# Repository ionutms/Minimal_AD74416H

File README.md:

# Minimal_AD74416H

## Overview

This repository contains a minimal KiCad design project for the Analog Devices AD74416H, a quad-channel, software-configurable input and output device with HART modem capabilities. The project includes schematic designs and PCB layout files for implementing this versatile analog I/O device.

## Disclaimer

> [!NOTE]
> This project is provided "as is" and without any warranty, express or implied. For more details, please see the [LICENSE](LICENSE) file.

## About the AD74416H

The AD74416H from Analog Devices is a quad-channel, software-configurable input/output solution for building and process control applications. It integrates a 24-bit, sigma-delta (Σ-Δ) analog-to-digital converter (ADC) and four 16-bit digital-to-analog converters (DACs).

Key features include:

- **Software-Configurable Channels:** Each of the four channels can be independently configured as:
  - Analog Input (Voltage or Current)
  - Analog Output (Voltage or Current)
  - Digital Input
  - Digital Output
  - 2- or 3-wire Resistance Temperature Detector (RTD) and Thermocouple measurements
- **HART Compatibility:** Each channel has an integrated HART (Highway Addressable Remote Transducer) modem.
- **Integrated Converters:** The device includes a 16-bit digital-to-analog converter (DAC) per channel and a single 24-bit sigma-delta (Σ-Δ) analog-to-digital converter (ADC).
- **Communication:** All input, output, and HART communications for the four channels are handled through a single SPI-compatible interface. It is possible to address up to four AD74416H devices on a single SPI bus.
- **Power Efficiency:** It features adaptive power switching, which can lower power dissipation by up to 40%.
- **Robustness and Diagnostics:** Features on-chip diagnostics like open-circuit and short-circuit detection and an internal temperature sensor.
- **Operating Temperature Range:** -40°C to +105°C.
- **Package:** Available in a 64-lead LFCSP package.

## Project Structure

```
minimal_ad74416h/
├── minimal_ad74416h.kicad_pro                     # Project configuration file
├── minimal_ad74416h.kicad_sch                     # Main schematic file
├── AD74416H.kicad_sch                             # AD74416H symbol definition
├── Front End Channel 1.kicad_sch                  # Channel-specific schematic
├── Power Supply and Digital Interface.kicad_sch   # Power and interface schematic
├── minimal_ad74416h.kicad_pcb                     # PCB layout file
├── fp-lib-table                                   # Footprint library table
├── sym-lib-table                                  # Symbol library table
├── docs/                                          # Documentation files
│   ├── bom/                                       # Bill of Materials
│   │   └── minimal_ad74416h_ibom.html             # Interactive BOM file
│   ├── pictures/                                  # Images and photos
│   │   ├── 1_minimal_ad74416h_side.png            # Side view of PCB
│   │   ├── 2_minimal_ad74416h_top.png             # Top view of PCB
│   │   └── 3_minimal_ad74416h_bottom.png          # Bottom view of PCB
│   └── schematics/                                # Schematic PDF exports
│       └── minimal_ad74416h_schematics.pdf        # Complete schematics PDF
└── KiCAD_Symbols_Generator/                       # Submodule for symbol generation from CSV data
```

## Project Features

This design provides a minimal implementation of the AD74416H with:

- Proper power supply connections
- Reference voltage generation
- Basic channel configuration
- HART communication interface
- Standard footprint for the 64-pin LFCSP package

## Getting Started

### Prerequisites

- [KiCad EDA](https://www.kicad.org/) version 9.0 or later installed on your system
- Git (for cloning the repository and submodule management)

### Opening the Project

1. **Clone the repository** (including submodules):
   ```bash
   git clone --recursive https://github.com/ionutms/Minimal_AD74416H.git
   ```
   
   If you've already cloned the repository without submodules, initialize them with:
   ```bash
   git submodule init
   git submodule update
   ```

2. **Open the project in KiCad**:
   - Launch KiCad
   - Click "Open Existing Project"
   - Navigate to the cloned repository folder
   - Select the `minimal_ad74416h.kicad_pro` file

3. **Explore the design**:
   - Open the schematic editor to view the circuit design
   - Open the PCB editor to view the board layout
   - Review the symbol and footprint libraries used in the design

### Project Files

- **Main schematic**: `minimal_ad74416h.kicad_sch` - Contains the primary circuit design with the AD74416H and support components
- **Channel schematic**: `Front End Channel 1.kicad_sch` - Detailed implementation of one channel with protection and filtering
- **Power schematic**: `Power Supply and Digital Interface.kicad_sch` - Power supply and digital interface circuits
- **PCB layout**: `minimal_ad74416h.kicad_pcb` - Physical board design file with proper component placement
- **Project configuration**: `minimal_ad74416h.kicad_pro` - KiCad project settings

## Dependencies

This project has the following dependencies:

### 1. KiCAD Symbols Generator

This repository uses [KiCAD_Symbols_Generator](https://github.com/ionutms/KiCAD_Symbols_Generator) as a submodule for custom symbol generation.

To initialize the submodule after cloning this repository:

```bash
git submodule update --init --recursive
```

### 2. 3D Models

This project requires the [3D_Models_Vault](https://github.com/ionutms/3D_Models_Vault) repository for 3D models.

#### Setup for KiCAD 9:

1. Clone the 3D models repository:
   ```bash
   git clone https://github.com/ionutms/3D_Models_Vault.git
   ```

2. In KiCAD 9, add an environment variable:
   - Variable name: `KICAD9_3D_MODELS_VAULT`
   - Variable value: Full path to where you cloned the 3D_Models_Vault repository

## Usage

After setting up the dependencies, open the project in KiCad 9 to access all features including the 3D models.

## Symbol Generator Submodule

This project includes the KiCAD_Symbols_Generator as a submodule, which provides tools for generating KiCad symbols from CSV data files. For more information on using this tool, see the [KiCAD_Symbols_Generator documentation](minimal_ad74416h/KiCAD_Symbols_Generator/README.md).

## Documentation

The `docs` folder contains:
- Schematic PDF exports
- Images and photos of the design

## Visuals

The following images showcase the PCB design from different perspectives:

*Top View of the PCB*

*Side View of the PCB*

*Bottom View of the PCB*

## License

This project is licensed under the MIT License - see the [LICENSE](LICENSE) file for details.

## References

- [AD74416H Datasheet](https://www.analog.com/media/en/technical-documentation/data-sheets/ad74416h.pdf)
- [KiCad EDA](https://www.kicad.org/)

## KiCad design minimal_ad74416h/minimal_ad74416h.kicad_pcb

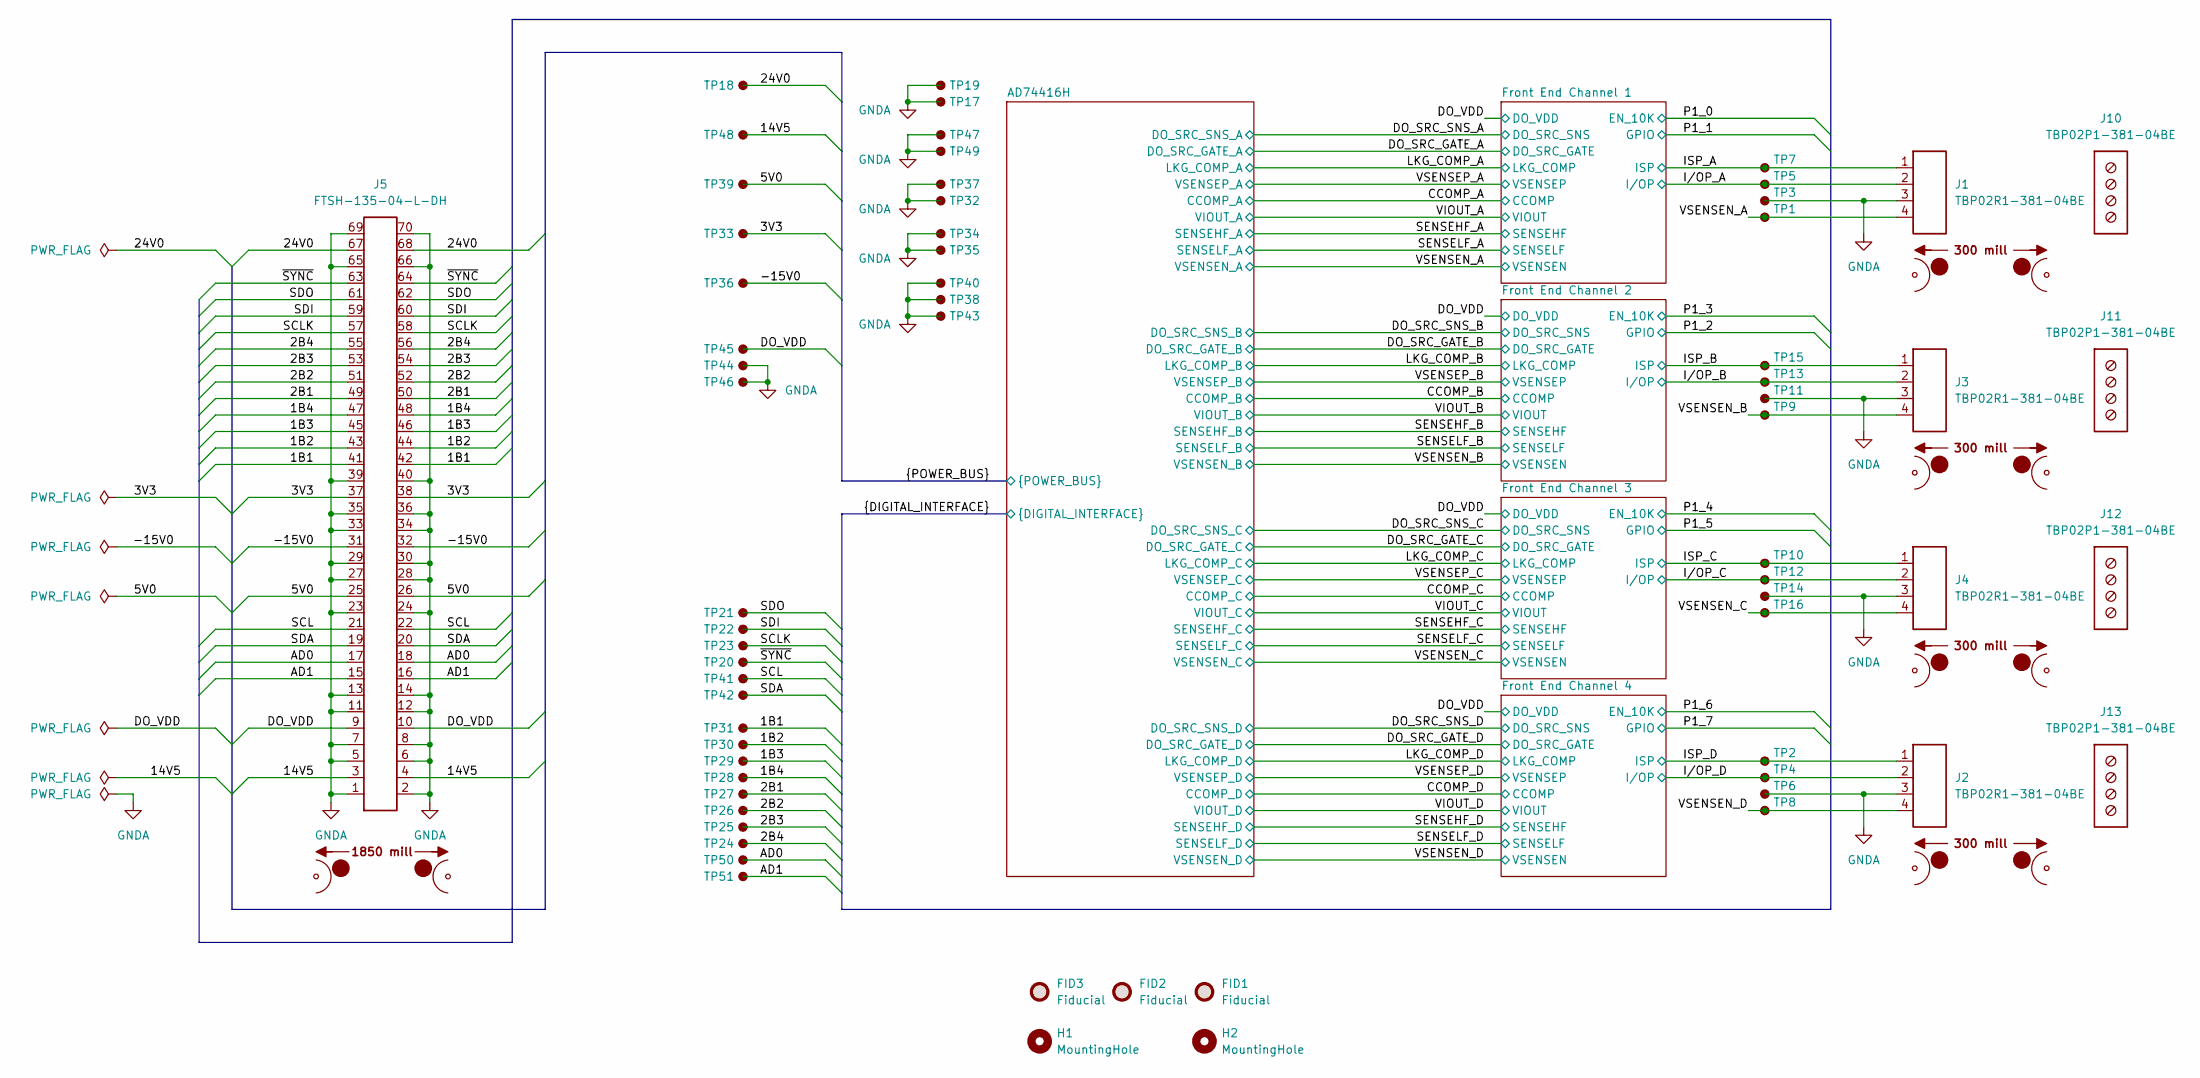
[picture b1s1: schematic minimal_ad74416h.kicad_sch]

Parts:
FID1, FID2, FID3: Fiducial; Fiducial_0.5mm_Mask1mm
H1, H2: MountingHole; MountingHole_3.2mm_M3
J1, J2, J3, J4: TBP02R1-381-04BE; Current Rating (A) 8.0; Voltage Rating (V) 300; MPN TBP02R1-381-04BE
J5: FTSH-135-04-L-DH; Current Rating (A) 5.2; Voltage Rating (V) 300; MPN FTSH-135-04-L-DH
J10, J11, J12, J13: TBP02P1-381-04BE; Current Rating (A) 8.0; Voltage Rating (V) 300; MPN TBP02P1-381-04BE
MB1, MB2, MB3, MB4: mouse-bite-50mil-300mil
MB5: mouse-bite-50mil-1850mil
TP1, TP2, TP3, TP4, TP5, TP6, TP7, TP8, TP9, TP10, TP11, TP12, TP13, TP14, TP15, TP16, TP17, TP18, TP19, TP20, TP21, TP22, TP23, TP24, TP25, TP26, TP27, TP28, TP29, TP30, TP31, TP32, TP33, TP34, TP35, TP36, TP37, TP38, TP39, TP40, TP41, TP42, TP43, TP44, TP45, TP46, TP47, TP48, TP49, TP50, TP51: TestPoint; TestPoint_THTPad_Castelated

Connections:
/1B1: J5.41, J5.42, TP31.1; also elsewhere on the board
/1B2: J5.43, J5.44, TP30.1; also elsewhere on the board
/1B3: J5.45, J5.46, TP29.1; also elsewhere on the board
/1B4: J5.47, J5.48, TP28.1; also elsewhere on the board
/2B1: J5.49, J5.50, TP27.1; also elsewhere on the board
/2B2: J5.51, J5.52, TP26.1; also elsewhere on the board
/2B3: J5.53, J5.54, TP25.1; also elsewhere on the board
/2B4: J5.55, J5.56, TP24.1; also elsewhere on the board
/3V3: J5.37, J5.38, TP33.1; also elsewhere on the board
/5V0: J5.25, J5.26, TP39.1; also elsewhere on the board
/14V5: J5.3, J5.4, TP48.1; also elsewhere on the board
/24V0: J5.67, J5.68, TP18.1; also elsewhere on the board
/-15V0: J5.31, J5.32, TP36.1; also elsewhere on the board
/AD0: J5.17, J5.18, TP50.1; also elsewhere on the board
/AD1: J5.15, J5.16, TP51.1; also elsewhere on the board
/DO_VDD: J5.9, J5.10, TP45.1; also elsewhere on the board
/ISP_A: J1.1, TP7.1; also elsewhere on the board
/ISP_B: J3.1, TP15.1; also elsewhere on the board
/ISP_C: J4.1, TP10.1; also elsewhere on the board
/ISP_D: J2.1, TP2.1; also elsewhere on the board
/I/OP_A: J1.2, TP5.1; also elsewhere on the board
/I/OP_B: J3.2, TP13.1; also elsewhere on the board
/I/OP_C: J4.2, TP12.1; also elsewhere on the board
/I/OP_D: J2.2, TP4.1; also elsewhere on the board
/SCL: J5.21, J5.22, TP41.1; also elsewhere on the board
/SCLK: J5.57, J5.58, TP23.1; also elsewhere on the board
/SDA: J5.19, J5.20, TP42.1; also elsewhere on the board
/SDI: J5.59, J5.60, TP22.1; also elsewhere on the board
/SDO: J5.61, J5.62, TP21.1; also elsewhere on the board
/VSENSEN_A: J1.4, TP1.1; also elsewhere on the board
/VSENSEN_B: J3.4, TP9.1; also elsewhere on the board
/VSENSEN_C: J4.4, TP16.1; also elsewhere on the board
/VSENSEN_D: J2.4, TP8.1; also elsewhere on the board
/~SYNC: J5.63, J5.64, TP20.1; also elsewhere on the board
GNDA: J1.3, J2.3, J3.3, J4.3, J5.1, J5.2, J5.5, J5.6, J5.7, J5.8, J5.11, J5.12, J5.13, J5.14, J5.23, J5.24, J5.27, J5.28, J5.29, J5.30, J5.33, J5.34, J5.35, J5.36, J5.39, J5.40, J5.65, J5.66, J5.69, J5.70, TP3.1, TP6.1, TP11.1, TP14.1, TP17.1, TP19.1, TP32.1, TP34.1, TP35.1, TP37.1, TP38.1, TP40.1, TP43.1, TP44.1, TP46.1, TP47.1, TP49.1; also elsewhere on the board

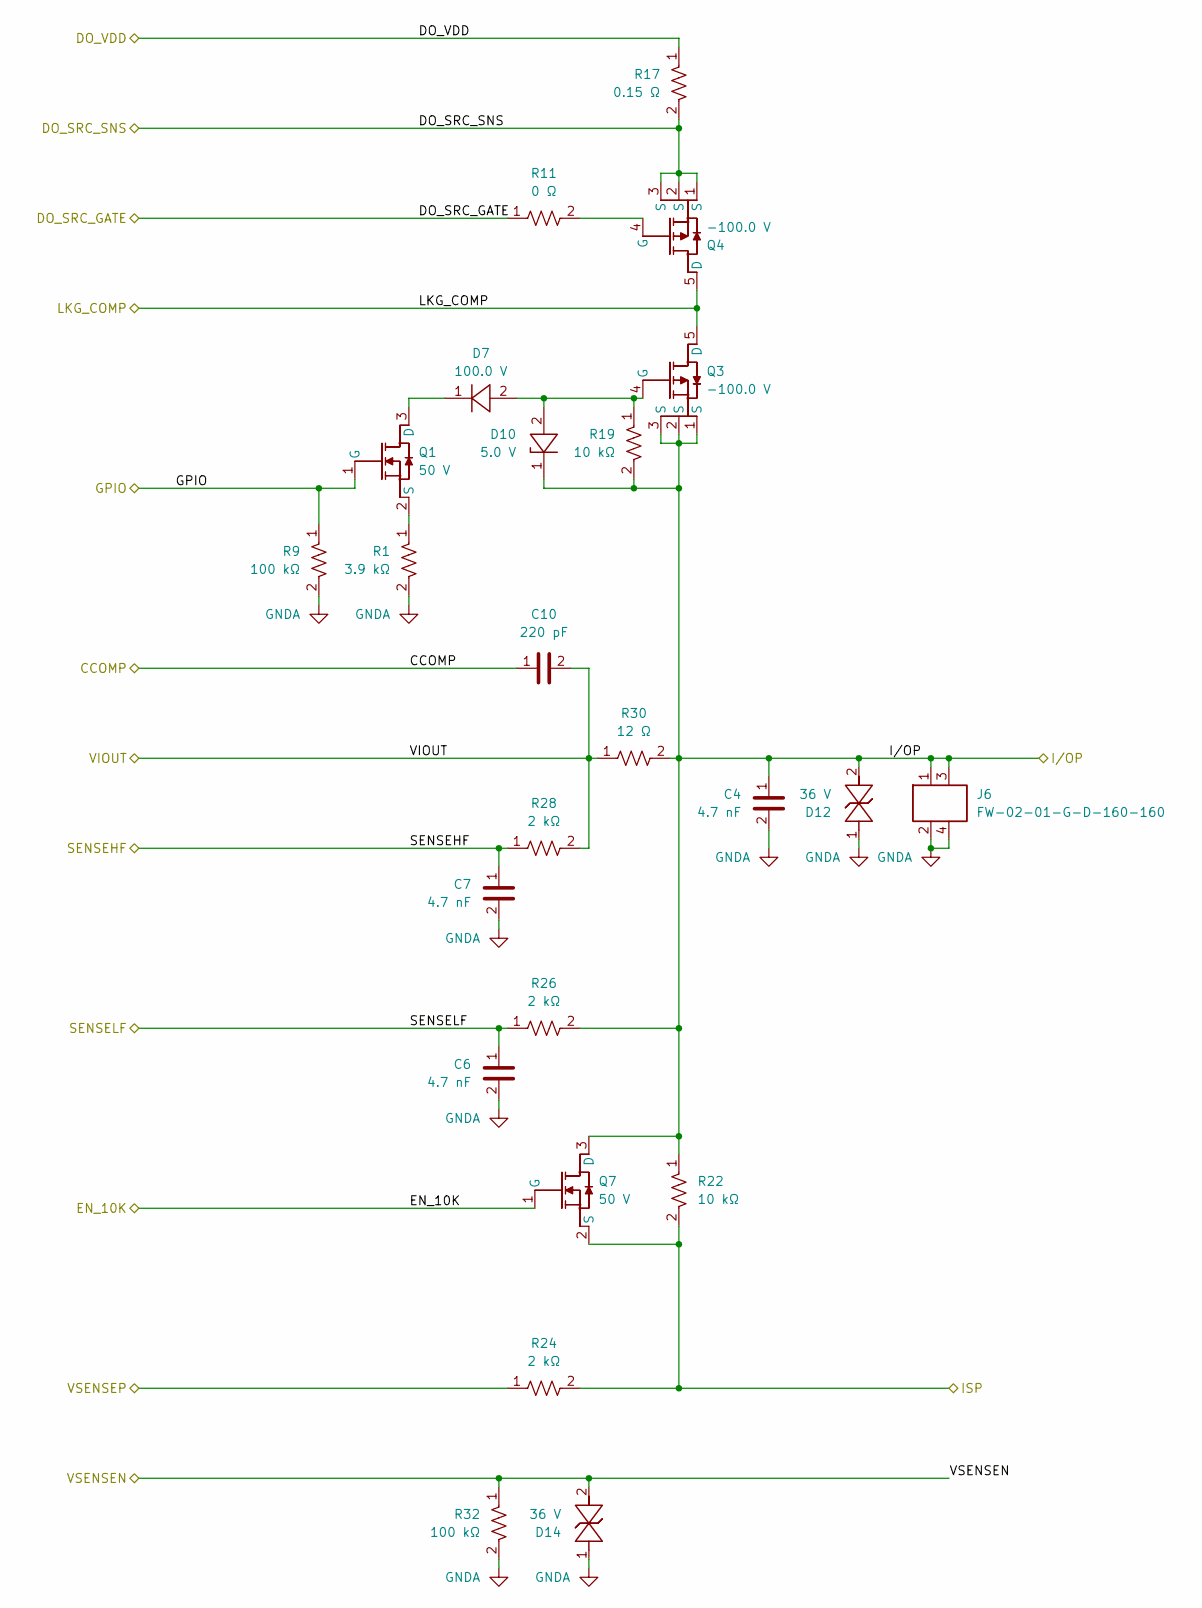
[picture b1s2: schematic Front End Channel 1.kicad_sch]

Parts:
C4, C6, C7: 4.7 nF; C_0603_1608Metric; Tolerance 10%; Voltage Rating 100V; MPN VJ0603Y472KXBAC
C10: 220 pF; C_0603_1608Metric; Tolerance 5%; Voltage Rating 50V; MPN CC0603JRNPO9BN221
D7: 100.0 V; DO-219AD; MPN MSE1PB-M3/89A
D10: 5.0 V; SOD323; MPN ESD9M5.0ST5G
D12, D14: 36 V; DO-214AA; MPN SMBJ36CA
J6: FW-02-01-G-D-160-160; Current Rating (A) 5.2; Voltage Rating (V) 300; MPN FW-02-01-G-D-160-160
Q1, Q7: 50 V; SOT23-3; MPN BSS138-7-F
Q3, Q4: -100.0 V; PowerPAK 1212-8; MPN SI7113ADN-T1-GE3
R1: 3.9 kΩ; R_0402_1005Metric; Tolerance 1%; Voltage Rating 50V; MPN ERJ-2RKF3901X
R9, R32: 100 kΩ; R_0402_1005Metric; Tolerance 5%; Voltage Rating 50V; MPN RMCF0402JT100K
R11: 0 Ω; R_0402_1005Metric; Tolerance 5%; Voltage Rating 50V; MPN ERJ-2GE0R00X
R17: 0.15 Ω; R_1206_3216Metric; Tolerance 1%; Voltage Rating 200; MPN CRM1206-FX-R150ELF
R19, R22: 10 kΩ; R_0402_1005Metric; Voltage Rating 50V; Tolerance 1%; MPN ERJ-2RKF1002X
R24, R26: 2 kΩ; R_0402_1005Metric; Tolerance 1%; Voltage Rating 50V; MPN ERJ-2RKF2001X
R28: 2 kΩ; R_0603_1608Metric; Tolerance 0.01%; Voltage Rating 75V; MPN RNCF0603TKY2K00
R30: 12 Ω; R_0805_2012Metric; Tolerance 0.1%; Voltage Rating 150V; MPN RT0805BRB0712RL

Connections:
/CCOMP_A: C10.1; also elsewhere on the board
/DO_SRC_GATE_A: R11.1; also elsewhere on the board
/DO_SRC_SNS_A: Q4.1 (S), Q4.2 (S), Q4.3 (S), R17.2; also elsewhere on the board
/DO_VDD: R17.1; also elsewhere on the board
/ISP_A: Q7.2 (S), R22.2, R24.2; also elsewhere on the board
/I/OP_A: C4.1, D10.1, D12.2, J6.1, J6.3, Q3.1 (S), Q3.2 (S), Q3.3 (S), Q7.3 (D), R19.2, R22.1, R26.2, R30.2; also elsewhere on the board
/LKG_COMP_A: Q3.5 (D), Q4.5 (D); also elsewhere on the board
/P1_0: Q7.1 (G); also elsewhere on the board
/P1_1: Q1.1 (G), R9.1; also elsewhere on the board
/SENSEHF_A: C7.1, R28.1; also elsewhere on the board
/SENSELF_A: C6.1, R26.1; also elsewhere on the board
/VIOUT_A: C10.2, R28.2, R30.1; also elsewhere on the board
/VSENSEN_A: D14.2, R32.1; also elsewhere on the board
/VSENSEP_A: R24.1; also elsewhere on the board
GNDA: C4.2, C6.2, C7.2, D12.1, D14.1, J6.2, J6.4, R1.2, R9.2, R32.2; also elsewhere on the board
unnamed: D7.1, Q1.3 (D)
unnamed: Q1.2 (S), R1.1
unnamed: D7.2, D10.2, Q3.4 (G), R19.1
unnamed: Q4.4 (G), R11.2

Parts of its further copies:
C5, C8, C9, C19, C20, C21, C22, C23, C24: 4.7 nF; C_0603_1608Metric; Tolerance 10%; Voltage Rating 100V; MPN VJ0603Y472KXBAC
C11, C16, C17: 220 pF; C_0603_1608Metric; Tolerance 5%; Voltage Rating 50V; MPN CC0603JRNPO9BN221
D8, D22, D23: 100.0 V; DO-219AD; MPN MSE1PB-M3/89A
D11, D20, D21: 5.0 V; SOD323; MPN ESD9M5.0ST5G
D13, D15, D16, D17, D18, D19: 36 V; DO-214AA; MPN SMBJ36CA
J7, J8, J9: FW-02-01-G-D-160-160; Current Rating (A) 5.2; Voltage Rating (V) 300; MPN FW-02-01-G-D-160-160
Q2, Q8, Q9, Q10, Q15, Q16: 50 V; SOT23-3; MPN BSS138-7-F
Q5, Q6, Q11, Q12, Q13, Q14: -100.0 V; PowerPAK 1212-8; MPN SI7113ADN-T1-GE3
R2, R33, R34, R35, R53, R55: 100 kΩ; R_0402_1005Metric; Tolerance 5%; Voltage Rating 50V; MPN RMCF0402JT100K
R10, R52, R56: 3.9 kΩ; R_0402_1005Metric; Tolerance 1%; Voltage Rating 50V; MPN ERJ-2RKF3901X
R12, R23, R44, R45, R47, R50: 10 kΩ; R_0402_1005Metric; Voltage Rating 50V; Tolerance 1%; MPN ERJ-2RKF1002X
R16, R48, R49: 0.15 Ω; R_1206_3216Metric; Tolerance 1%; Voltage Rating 200; MPN CRM1206-FX-R150ELF
R20, R46, R51: 0 Ω; R_0402_1005Metric; Tolerance 5%; Voltage Rating 50V; MPN ERJ-2GE0R00X
R25, R27, R40, R41, R42, R43: 2 kΩ; R_0402_1005Metric; Tolerance 1%; Voltage Rating 50V; MPN ERJ-2RKF2001X
R29, R38, R39: 2 kΩ; R_0603_1608Metric; Tolerance 0.01%; Voltage Rating 75V; MPN RNCF0603TKY2K00
R31, R36, R37: 12 Ω; R_0805_2012Metric; Tolerance 0.1%; Voltage Rating 150V; MPN RT0805BRB0712RL

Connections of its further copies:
/CCOMP_B: C16.1; also elsewhere on the board
/CCOMP_C: C17.1; also elsewhere on the board
/CCOMP_D: C11.1; also elsewhere on the board
/DO_SRC_GATE_B: R46.1; also elsewhere on the board
/DO_SRC_GATE_C: R51.1; also elsewhere on the board
/DO_SRC_GATE_D: R20.1; also elsewhere on the board
/DO_SRC_SNS_B: Q12.1 (S), Q12.2 (S), Q12.3 (S), R49.2; also elsewhere on the board
/DO_SRC_SNS_C: Q13.1 (S), Q13.2 (S), Q13.3 (S), R48.2; also elsewhere on the board
/DO_SRC_SNS_D: Q5.1 (S), Q5.2 (S), Q5.3 (S), R16.2; also elsewhere on the board
/DO_VDD: R16.1, R48.1, R49.1; also elsewhere on the board
/ISP_B: Q9.2 (S), R42.2, R44.2; also elsewhere on the board
/ISP_C: Q10.2 (S), R43.2, R45.2; also elsewhere on the board
/ISP_D: Q8.2 (S), R23.2, R25.2; also elsewhere on the board
/I/OP_B: C23.1, D18.2, D20.1, J7.1, J7.3, Q9.3 (D), Q11.1 (S), Q11.2 (S), Q11.3 (S), R36.2, R40.2, R44.1, R50.2; also elsewhere on the board
/I/OP_C: C24.1, D19.2, D21.1, J8.1, J8.3, Q10.3 (D), Q14.1 (S), Q14.2 (S), Q14.3 (S), R37.2, R41.2, R45.1, R47.2; also elsewhere on the board
/I/OP_D: C5.1, D11.1, D13.2, J9.1, J9.3, Q6.1 (S), Q6.2 (S), Q6.3 (S), Q8.3 (D), R12.2, R23.1, R27.2, R31.2; also elsewhere on the board
/LKG_COMP_B: Q11.5 (D), Q12.5 (D); also elsewhere on the board
/LKG_COMP_C: Q13.5 (D), Q14.5 (D); also elsewhere on the board
/LKG_COMP_D: Q5.5 (D), Q6.5 (D); also elsewhere on the board
/P1_2: Q15.1 (G), R55.1; also elsewhere on the board
/P1_3: Q9.1 (G); also elsewhere on the board
/P1_4: Q10.1 (G); also elsewhere on the board
/P1_5: Q16.1 (G), R53.1; also elsewhere on the board
/P1_6: Q8.1 (G); also elsewhere on the board
/P1_7: Q2.1 (G), R2.1; also elsewhere on the board
/SENSEHF_B: C20.1, R38.1; also elsewhere on the board
/SENSEHF_C: C21.1, R39.1; also elsewhere on the board
/SENSEHF_D: C8.1, R29.1; also elsewhere on the board
/SENSELF_B: C19.1, R40.1; also elsewhere on the board
/SENSELF_C: C22.1, R41.1; also elsewhere on the board
/SENSELF_D: C9.1, R27.1; also elsewhere on the board
/VIOUT_B: C16.2, R36.1, R38.2; also elsewhere on the board
/VIOUT_C: C17.2, R37.1, R39.2; also elsewhere on the board
/VIOUT_D: C11.2, R29.2, R31.1; also elsewhere on the board
/VSENSEN_B: D16.2, R34.1; also elsewhere on the board
/VSENSEN_C: D17.2, R35.1; also elsewhere on the board
/VSENSEN_D: D15.2, R33.1; also elsewhere on the board
/VSENSEP_B: R42.1; also elsewhere on the board
/VSENSEP_C: R43.1; also elsewhere on the board
/VSENSEP_D: R25.1; also elsewhere on the board
GNDA: C5.2, C8.2, C9.2, C19.2, C20.2, C21.2, C22.2, C23.2, C24.2, D13.1, D15.1, D16.1, D17.1, D18.1, D19.1, J7.2, J7.4, J8.2, J8.4, J9.2, J9.4, R2.2, R10.2, R33.2, R34.2, R35.2, R52.2, R53.2, R55.2, R56.2; also elsewhere on the board
unnamed: D8.1, Q2.3 (D)
unnamed: Q2.2 (S), R10.1
unnamed: Q5.4 (G), R20.2
unnamed: D8.2, D11.2, Q6.4 (G), R12.1
unnamed: D20.2, D22.2, Q11.4 (G), R50.1
unnamed: Q12.4 (G), R46.2
unnamed: Q13.4 (G), R51.2
unnamed: D21.2, D23.2, Q14.4 (G), R47.1
unnamed: D22.1, Q15.3 (D)
unnamed: Q15.2 (S), R52.1
unnamed: D23.1, Q16.3 (D)
unnamed: Q16.2 (S), R56.1

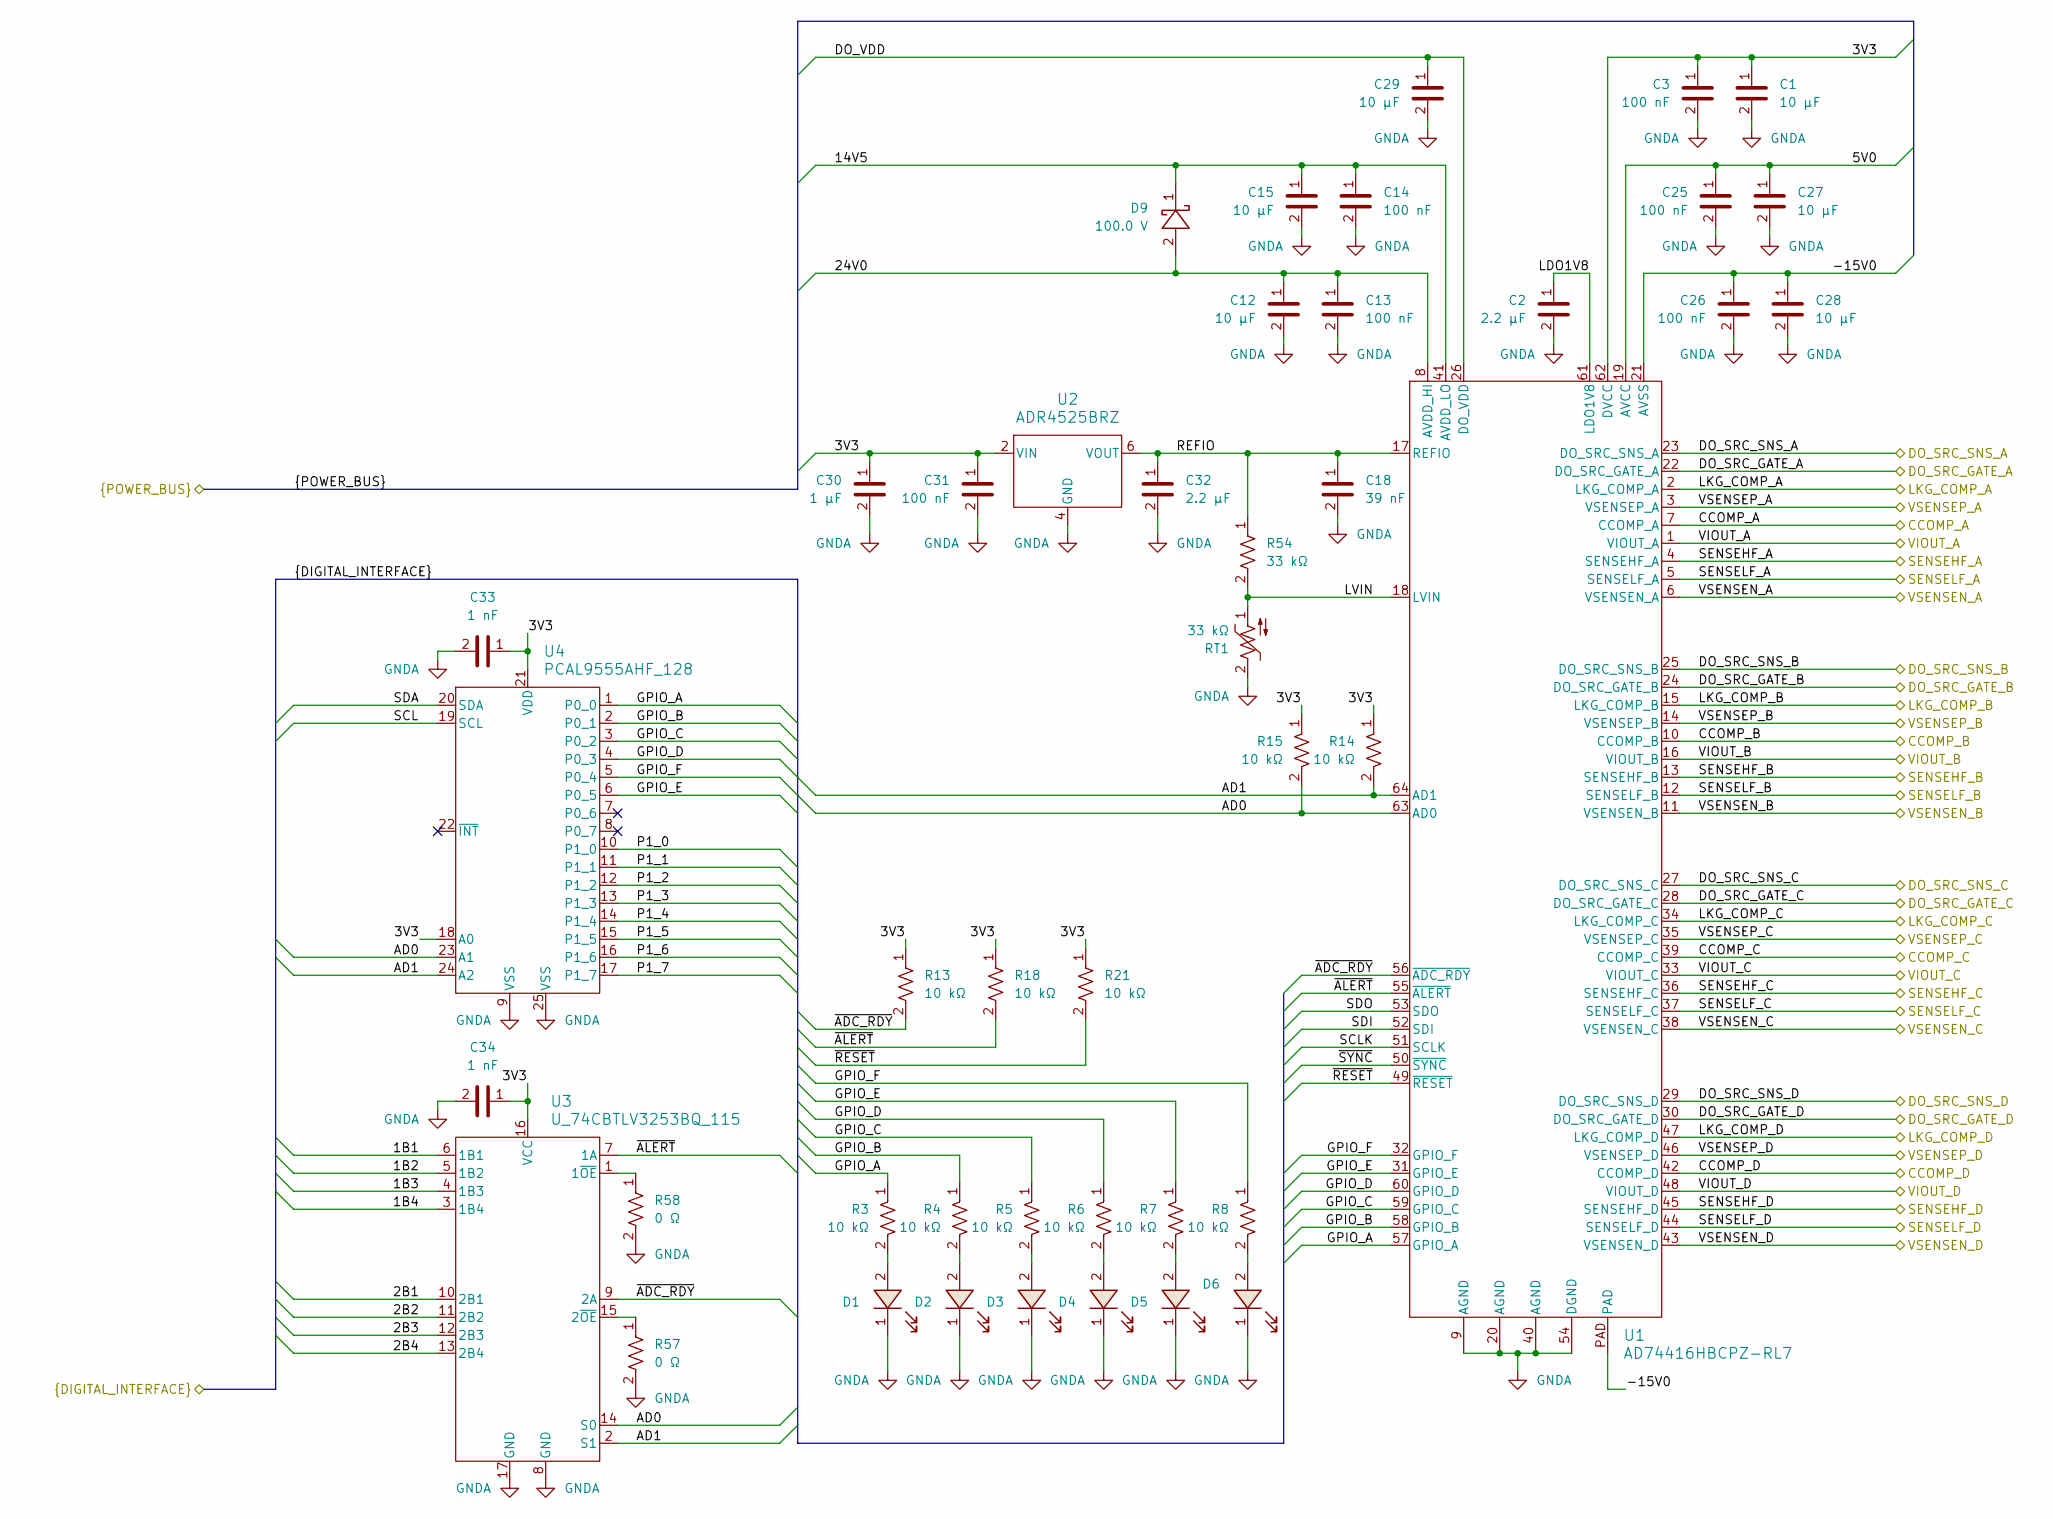
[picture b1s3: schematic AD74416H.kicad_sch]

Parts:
C1, C12, C15, C27, C28: 10 µF; C_0805_125_2012Metric; Voltage Rating DC 50 VDC; Tolerance 10%; MPN GRM21BR61H106KE43L
C2: 2.2 µF; C_0805_2012Metric; Tolerance 10%; Voltage Rating 35V; MPN CGA4J1X7R1V225K125AC
C3, C13, C14, C25, C26, C31: 100 nF; C_0402_1005Metric; Voltage Rating DC 50 VDC; Tolerance 10%; MPN GCM155R71H104KE02D
C18: 39 nF; C_0402_1005Metric; Tolerance 10%; Voltage Rating 16V; MPN KGM05AR71C393KH
C29: 10 µF; C_1210_250_3225Metric; Tolerance 10%; Voltage Rating 100V; MPN GRM32EC72A106KE05L
C30: 1 µF; C_0805_2012Metric; Tolerance 10%; Voltage Rating 100V; MPN GRJ21BC72A105KE11L
C32: 2.2 µF; C_0603_1608Metric; Tolerance 10%; Voltage Rating 10V; MPN C1608X7S1A225K080AC
C33, C34: 1 nF; C_0402_1005Metric; Tolerance 10%; Voltage Rating 50V; MPN GCM155R71H102KA37D
D1, D2, D3, D4, D5, D6: 2.1 V; LED_GREEN_0402_1005Metric; MPN APHHS1005CGCK
D9: 100.0 V; SOD_523; MPN BAT41KFILM
R3, R4, R5, R6, R7, R8, R13, R14, R15, R18, R21: 10 kΩ; R_0402_1005Metric; Voltage Rating 50V; Tolerance 1%; MPN ERJ-2RKF1002X
R54: 33 kΩ; R_0402_1005Metric; Tolerance 1%; Voltage Rating 50V; MPN ERJ-2RKF3302X
R57, R58: 0 Ω; R_0402_1005Metric; Tolerance 5%; Voltage Rating 50V; MPN ERJ-2GE0R00X
RT1: 33 kΩ; RT_0805_RT_2012Metric; Tolerance 5%; Voltage Rating 50V; MPN NTCS0805E3333JHT
U1: AD74416HBCPZ-RL7; CP-64-15_ADI; MPN AD74416HBCPZ-RL7
U2: ADR4525BRZ; R_8_ADI; MPN ADR4525BRZ
U3: U_74CBTLV3253BQ_115; DHVQFN16_SOT763-1_NEX; MPN 74CBTLV3253BQ,115
U4: PCAL9555AHF_128; HWQFN24_SOT994-1_NXP; MPN PCAL9555AHF,128

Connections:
/1B1: U3.6 (1B1); also elsewhere on the board
/1B2: U3.5 (1B2); also elsewhere on the board
/1B3: U3.4 (1B3); also elsewhere on the board
/1B4: U3.3 (1B4); also elsewhere on the board
/2B1: U3.10 (2B1); also elsewhere on the board
/2B2: U3.11 (2B2); also elsewhere on the board
/2B3: U3.12 (2B3); also elsewhere on the board
/2B4: U3.13 (2B4); also elsewhere on the board
/3V3: C1.1, C3.1, C30.1, C31.1, C33.1, C34.1, R13.1, R14.1, R15.1, R18.1, R21.1, U1.62 (DVCC), U2.2 (VIN), U3.16 (VCC), U4.18 (A0), U4.21 (VDD); also elsewhere on the board
/5V0: C25.1, C27.1, U1.19 (AVCC); also elsewhere on the board
/14V5: C14.1, C15.1, D9.1, U1.41 (AVDD_LO); also elsewhere on the board
/24V0: C12.1, C13.1, D9.2, U1.8 (AVDD_HI); also elsewhere on the board
/-15V0: C26.1, C28.1, U1.21 (AVSS), U1.PAD; also elsewhere on the board
/AD0: R15.2, U1.63 (AD0), U3.14 (S0), U4.23 (A1); also elsewhere on the board
/AD1: R14.2, U1.64 (AD1), U3.2 (S1), U4.24 (A2); also elsewhere on the board
/AD74416H/LDO1V8: C2.1, U1.61 (LDO1V8)
/AD74416H/LVIN: R54.2, RT1.1, U1.18 (LVIN)
/AD74416H/REFIO: C18.1, C32.1, R54.1, U1.17 (REFIO), U2.6 (VOUT)
/CCOMP_A: U1.7 (CCOMP_A); also elsewhere on the board
/CCOMP_B: U1.10 (CCOMP_B); also elsewhere on the board
/CCOMP_C: U1.39 (CCOMP_C); also elsewhere on the board
/CCOMP_D: U1.42 (CCOMP_D); also elsewhere on the board
/DO_SRC_GATE_A: U1.22 (DO_SRC_GATE_A); also elsewhere on the board
/DO_SRC_GATE_B: U1.24 (DO_SRC_GATE_B); also elsewhere on the board
/DO_SRC_GATE_C: U1.28 (DO_SRC_GATE_C); also elsewhere on the board
/DO_SRC_GATE_D: U1.30 (DO_SRC_GATE_D); also elsewhere on the board
/DO_SRC_SNS_A: U1.23 (DO_SRC_SNS_A); also elsewhere on the board
/DO_SRC_SNS_B: U1.25 (DO_SRC_SNS_B); also elsewhere on the board
/DO_SRC_SNS_C: U1.27 (DO_SRC_SNS_C); also elsewhere on the board
/DO_SRC_SNS_D: U1.29 (DO_SRC_SNS_D); also elsewhere on the board
/DO_VDD: C29.1, U1.26 (DO_VDD); also elsewhere on the board
/GPIO_A: R3.1, U1.57 (GPIO_A), U4.1 (P0_0)
/GPIO_B: R4.1, U1.58 (GPIO_B), U4.2 (P0_1)
/GPIO_C: R5.1, U1.59 (GPIO_C), U4.3 (P0_2)
/GPIO_D: R6.1, U1.60 (GPIO_D), U4.4 (P0_3)
/GPIO_E: R7.1, U1.31 (GPIO_E), U4.6 (P0_5)
/GPIO_F: R8.1, U1.32 (GPIO_F), U4.5 (P0_4)
/LKG_COMP_A: U1.2 (LKG_COMP_A); also elsewhere on the board
/LKG_COMP_B: U1.15 (LKG_COMP_B); also elsewhere on the board
/LKG_COMP_C: U1.34 (LKG_COMP_C); also elsewhere on the board
/LKG_COMP_D: U1.47 (LKG_COMP_D); also elsewhere on the board
/P1_0: U4.10 (P1_0); also elsewhere on the board
/P1_1: U4.11 (P1_1); also elsewhere on the board
/P1_2: U4.12 (P1_2); also elsewhere on the board
/P1_3: U4.13 (P1_3); also elsewhere on the board
/P1_4: U4.14 (P1_4); also elsewhere on the board
/P1_5: U4.15 (P1_5); also elsewhere on the board
/P1_6: U4.16 (P1_6); also elsewhere on the board
/P1_7: U4.17 (P1_7); also elsewhere on the board
/SCL: U4.19 (SCL); also elsewhere on the board
/SCLK: U1.51 (SCLK); also elsewhere on the board
/SDA: U4.20 (SDA); also elsewhere on the board
/SDI: U1.52 (SDI); also elsewhere on the board
/SDO: U1.53 (SDO); also elsewhere on the board
/SENSEHF_A: U1.4 (SENSEHF_A); also elsewhere on the board
/SENSEHF_B: U1.13 (SENSEHF_B); also elsewhere on the board
/SENSEHF_C: U1.36 (SENSEHF_C); also elsewhere on the board
/SENSEHF_D: U1.45 (SENSEHF_D); also elsewhere on the board
/SENSELF_A: U1.5 (SENSELF_A); also elsewhere on the board
/SENSELF_B: U1.12 (SENSELF_B); also elsewhere on the board
/SENSELF_C: U1.37 (SENSELF_C); also elsewhere on the board
/SENSELF_D: U1.44 (SENSELF_D); also elsewhere on the board
/VIOUT_A: U1.1 (VIOUT_A); also elsewhere on the board
/VIOUT_B: U1.16 (VIOUT_B); also elsewhere on the board
/VIOUT_C: U1.33 (VIOUT_C); also elsewhere on the board
/VIOUT_D: U1.48 (VIOUT_D); also elsewhere on the board
/VSENSEN_A: U1.6 (VSENSEN_A); also elsewhere on the board
/VSENSEN_B: U1.11 (VSENSEN_B); also elsewhere on the board
/VSENSEN_C: U1.38 (VSENSEN_C); also elsewhere on the board
/VSENSEN_D: U1.43 (VSENSEN_D); also elsewhere on the board
/VSENSEP_A: U1.3 (VSENSEP_A); also elsewhere on the board
/VSENSEP_B: U1.14 (VSENSEP_B); also elsewhere on the board
/VSENSEP_C: U1.35 (VSENSEP_C); also elsewhere on the board
/VSENSEP_D: U1.46 (VSENSEP_D); also elsewhere on the board
/~ADC_RDY: R13.2, U1.56 (~ADC_RDY), U3.9 (2A)
/~ALERT: R18.2, U1.55 (~ALERT), U3.7 (1A)
/~RESET: R21.2, U1.49 (~RESET)
/~SYNC: U1.50 (~SYNC); also elsewhere on the board
GNDA: C1.2, C2.2, C3.2, C12.2, C13.2, C14.2, C15.2, C18.2, C25.2, C26.2, C27.2, C28.2, C29.2, C30.2, C31.2, C32.2, C33.2, C34.2, D1.1, D2.1, D3.1, D4.1, D5.1, D6.1, R57.2, R58.2, RT1.2, U1.9 (AGND), U1.20 (AGND), U1.40 (AGND), U1.54 (DGND), U2.4 (GND), U3.8 (GND), U3.17 (GND), U4.9 (VSS), U4.25 (VSS); also elsewhere on the board
unnamed: D1.2, R3.2
unnamed: D2.2, R4.2
unnamed: D3.2, R5.2
unnamed: D4.2, R6.2
unnamed: D5.2, R7.2
unnamed: D6.2, R8.2
unnamed: R58.1, U3.1 (1~OE)
unnamed: R57.1, U3.15 (2~OE)

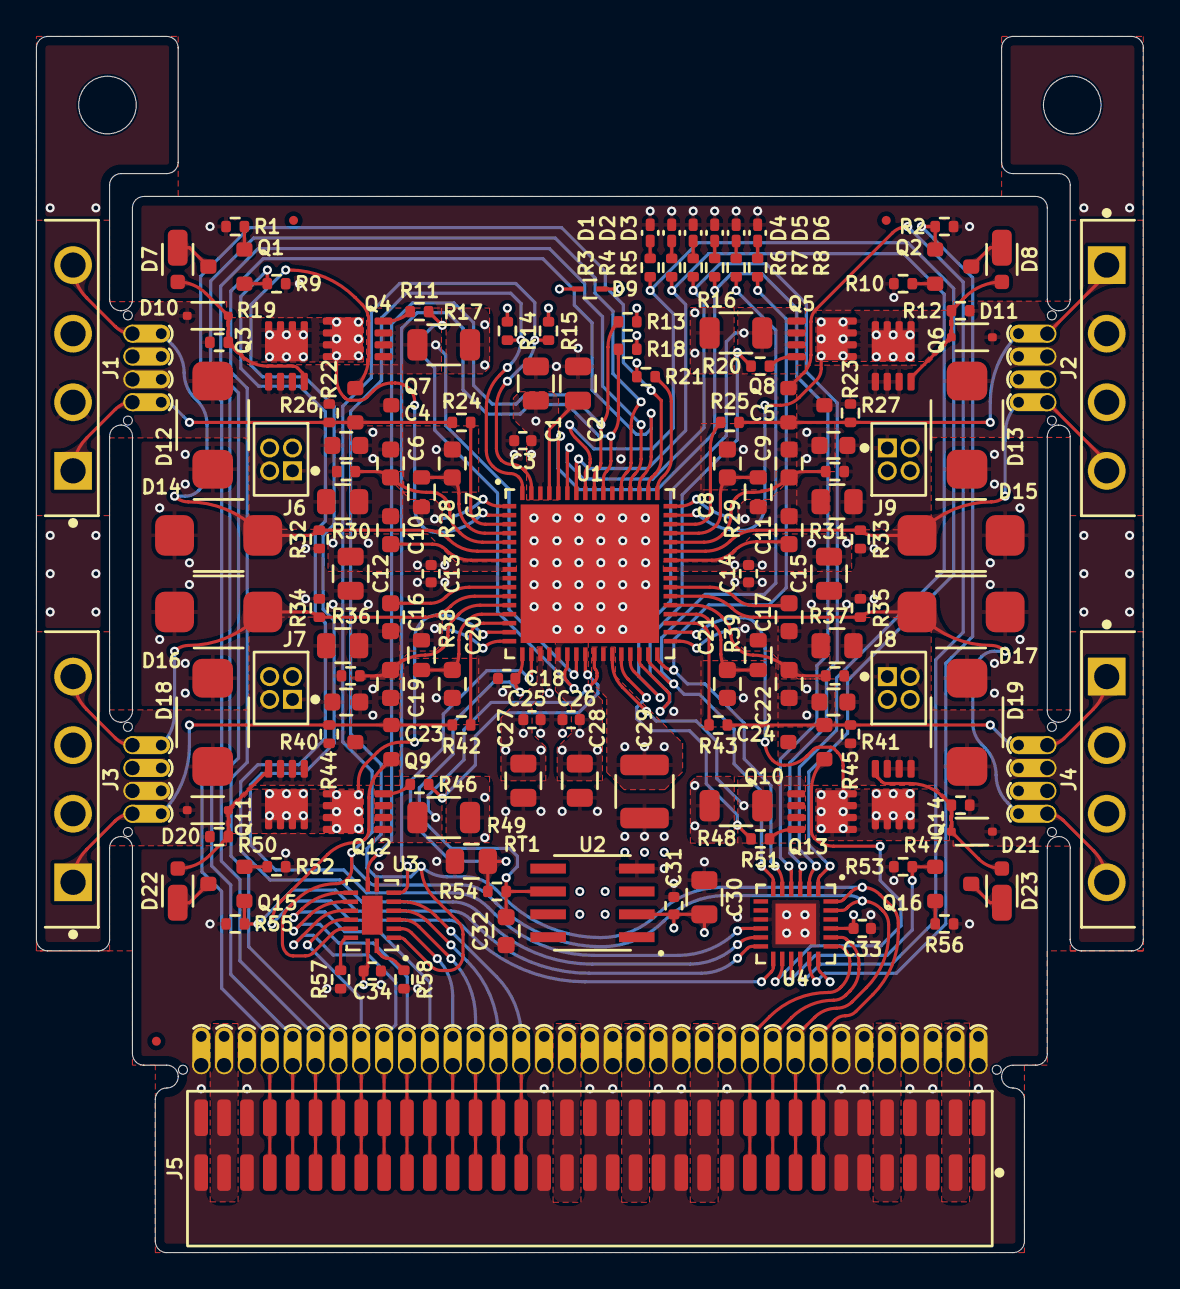
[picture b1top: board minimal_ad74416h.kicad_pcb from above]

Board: 4 copper layers, 61.5 x 67.6 mm, 210 parts (0 on the bottom side), 111 nets.

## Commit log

2025-08-08 add initial project
2025-08-08 Update KiCad documentation for minimal_ad74416h (schematics and PCB renders)
2025-08-08 minor changes
2025-08-09 backup
2025-08-09 update view config
2025-08-15 docs: completely rewrite README.md with comprehensive project documentation
2025-08-17 Update README to include images from docs folder
2025-08-18 Add bottom view PCB render to KiCad documentation workflow
2025-08-18 Add --side bottom parameter to PCB bottom view render
2025-08-18 Rename PCB render output files with numbered prefixes
2025-08-18 Update README.md with bottom view image and improved descriptions
2025-08-22 Update workflows: Trigger 3D models generation after documentation workflow completes
2025-08-28 Add support for KiCad Interactive HTML BOM generation in workflow
2025-08-28 Fix escaping in KiCad workflow file paths
2025-08-28 Improve Interactive HTML BOM generation in workflow: use pip install with fallback to direct clone
2025-08-28 Fix Interactive HTML BOM generation: add virtual display support and improve error handling
2025-08-28 Remove support for KiCad Interactive HTML BOM generation in workflow
2025-08-28 Add InteractiveHtmlBom installation step in workflow
2025-08-28 Fix InteractiveHtmlBom installation command
2025-08-28 Fix InteractiveHtmlBom installation by ensuring pip is available first
2025-08-28 Fix InteractiveHtmlBom installation by installing pip via system package manager
2025-08-28 Fix: Correctly escape quotes in workflow echo commands
2025-08-28 Feat: Add InteractiveHtmlBom installation to workflow
2025-08-28 Fix: Quote file paths in workflow
2025-08-28 Fix: Use sudo for apt-get in workflow
2025-08-28 Fix: Remove InteractiveHtmlBom installation from workflow
2025-08-28 Update KiCad Docker image version from V1.0 to V1.1 in GitHub workflows
2025-08-28 Revert KiCad Docker image version from V1.1 to V1.0 in GitHub workflows
2025-08-28 Add Interactive HTML BOM generation to KiCad documentation workflow
2025-08-28 Fix Interactive HTML BOM script path in KiCad documentation workflow
2025-08-28 Improve Interactive HTML BOM generation with better script detection and file handling
2025-08-28 Update KiCad job generation workflow with improved script detection
2025-08-28 Simplify Interactive HTML BOM generation by using Docker image's built-in wrapper script
2025-08-28 Update Interactive HTML BOM generation parameter from --output-name to --name-format
2025-08-28 Update Interactive HTML BOM generation to use PCB file instead of schematic file
2025-08-28 Organize documentation structure by moving BOM files to dedicated bom directory
2025-09-02 Update project documentation and schematic files
2025-09-02 Update README.md with additional device features and specifications
2025-09-10 Update Project Structure section in README.md with detailed file listings and aligned comments
2025-10-04 Add trigger-symbol-check workflow and update generate_kicad_jobs
2025-10-04 Update workflow files and KiCAD symbols generator
2025-10-04 Update KiCAD symbols generator
2025-10-05 chore: update workflows and kicad config from central repository
2025-10-12 Add front/back view rendering and update symbol check workflow
2025-10-12 Optimize workflow: Remove unnecessary symbol check requirements step
2025-10-18 Update KiCad configuration
2025-10-18 Update KiCad configuration settings
2025-10-23 Update KiCAD view zoom factors in config
2025-10-26 Enhance KiCad config with view settings
    Added detailed view configurations for different orientations including zoom factors, rotations, pans, and light elevations.
2025-10-26 Update kicad-config workflow settings
2025-10-26 Update kicad-config workflow settings - remove test view
2025-10-26 Resolve merge conflict in kicad-config.yml
2025-10-29 Update KiCAD configuration and project files
2025-10-29 Update KiCAD Symbols Generator submodule
2025-10-29 Add STEP file export and vault integration to 3D models workflow
2025-10-29 Update KiCad 3D models workflow with STEP export and vault integration
2025-10-29 Update KiCad 3D models workflow: enhance STEP file handling and size checking
2025-10-30 Sync changes between main and doc_workflow branches
